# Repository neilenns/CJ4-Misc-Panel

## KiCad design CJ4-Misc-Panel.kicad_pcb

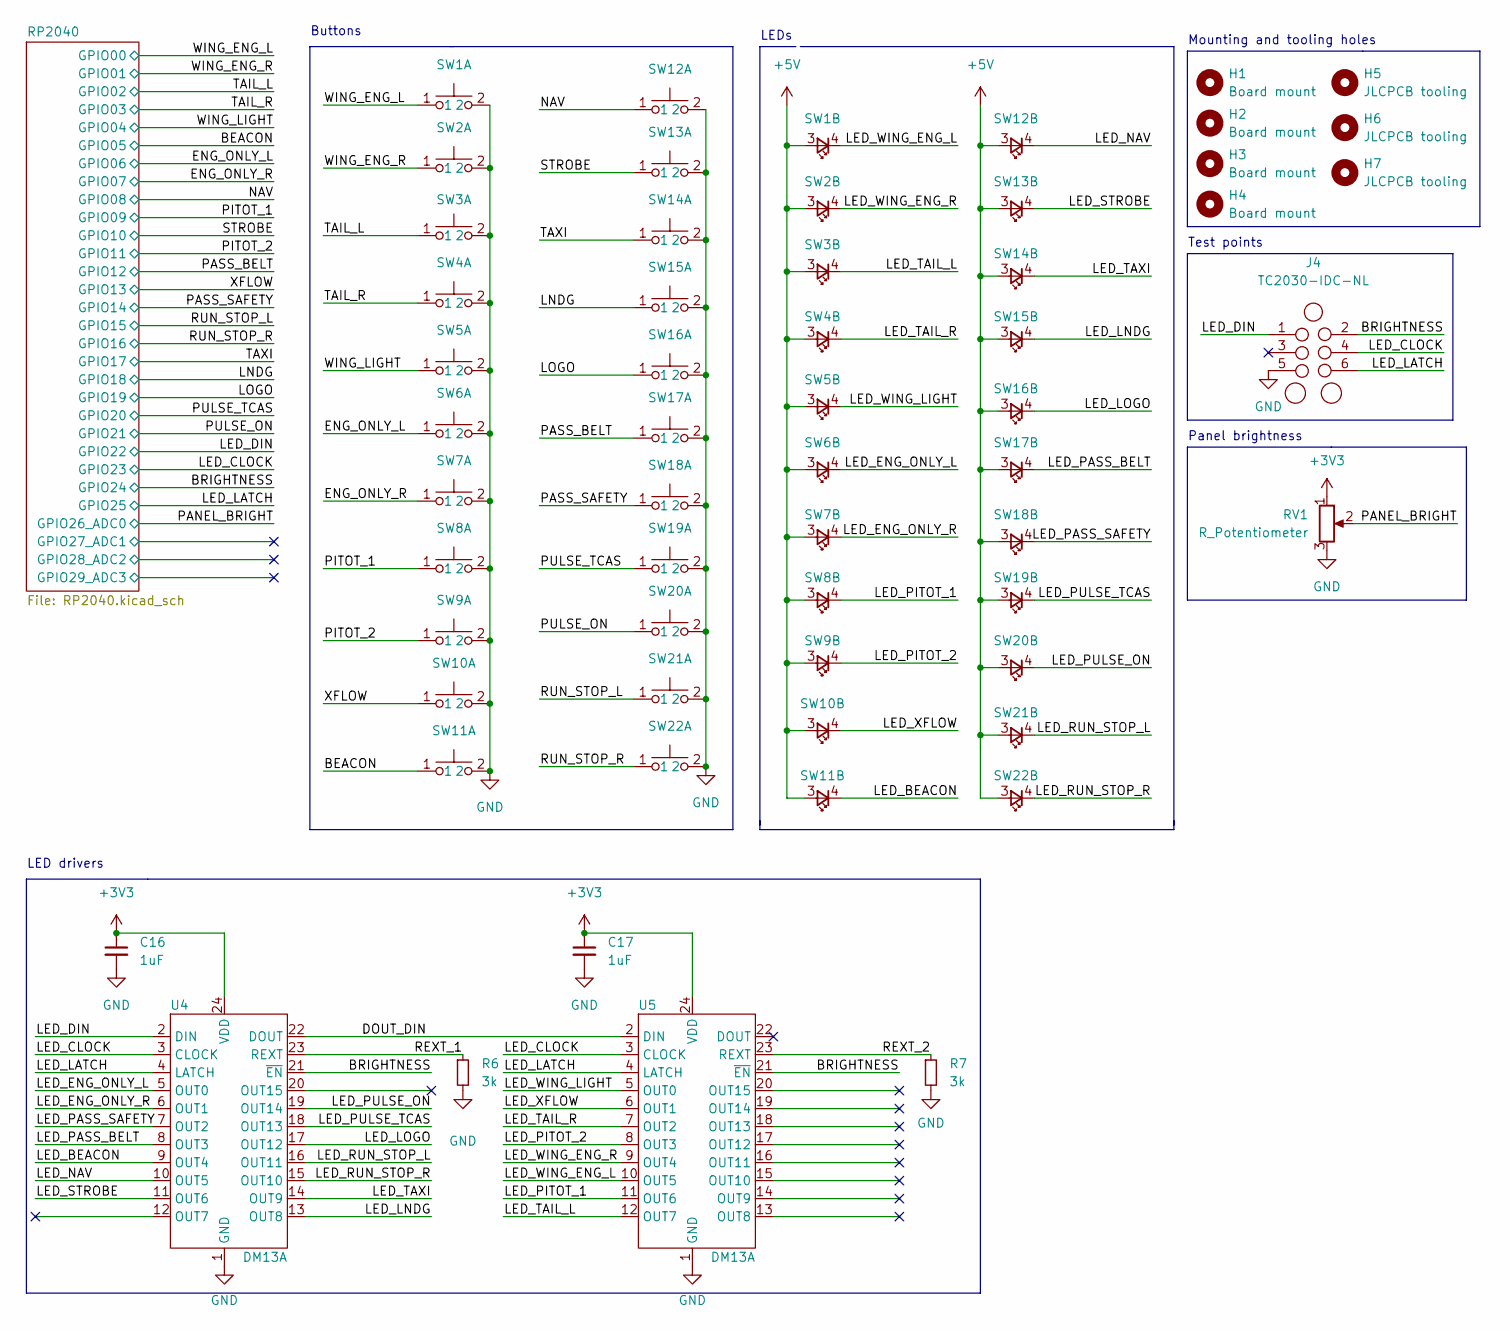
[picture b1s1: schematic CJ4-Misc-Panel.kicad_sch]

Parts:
C16, C17: 1uF; Perfect_0402; MPN - JLCPCB C52923
H1, H2, H3, H4: Board mount; MountingHole_3.2mm_M3
H5, H6, H7: JLCPCB tooling; JLCPCB_Tooling_Hole
J4: TC2030-IDC-NL; Tag-Connect_TC2030-IDC-NL_2x03_P1.27mm_Vertical
R6, R7: 3k; R_0805_2012Metric_Pad1.20x1.40mm_HandSolder; MPN - JLCPCB C17661; JLC 0805
RV1: R_Potentiometer; Potentiometer_Bourns_PTV09A-1_Single_Vertical
SW1, SW2, SW3, SW4, SW5, SW6, SW7, SW8, SW9, SW10, SW11, SW12, SW13, SW14, SW15, SW16, SW17, SW18, SW19, SW20, SW21, SW22: SW_PUSH_LED; SW_PUSH_LED_THT
U4, U5: DM13A; SSOP-24_3.9x8.7mm_P0.635mm

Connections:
+3V3: C16.1, C17.1, RV1.1, U4.24 (VDD), U5.24 (VDD); also elsewhere on the board
+5V: SW1.3, SW2.3, SW3.3, SW4.3, SW5.3, SW6.3, SW7.3, SW8.3, SW9.3, SW10.3, SW11.3, SW12.3, SW13.3, SW14.3, SW15.3, SW16.3, SW17.3, SW18.3, SW19.3, SW20.3, SW21.3, SW22.3; also elsewhere on the board
/BEACON: SW11.1; also elsewhere on the board
/BRIGHTNESS: J4.2, U4.21 (~EN), U5.21 (~EN); also elsewhere on the board
/DOUT_DIN: U4.22 (DOUT), U5.2 (DIN)
/ENG_ONLY_L: SW6.1; also elsewhere on the board
/ENG_ONLY_R: SW7.1; also elsewhere on the board
/LED_BEACON: SW11.4, U4.9 (OUT4)
/LED_CLOCK: J4.4, U4.3 (CLOCK), U5.3 (CLOCK); also elsewhere on the board
/LED_DIN: J4.1, U4.2 (DIN); also elsewhere on the board
/LED_ENG_ONLY_L: SW6.4, U4.5 (OUT0)
/LED_ENG_ONLY_R: SW7.4, U4.6 (OUT1)
/LED_LATCH: J4.6, U4.4 (LATCH), U5.4 (LATCH); also elsewhere on the board
/LED_LNDG: SW15.4, U4.13 (OUT8)
/LED_LOGO: SW16.4, U4.17 (OUT12)
/LED_NAV: SW12.4, U4.10 (OUT5)
/LED_PASS_BELT: SW17.4, U4.8 (OUT3)
/LED_PASS_SAFETY: SW18.4, U4.7 (OUT2)
/LED_PITOT_1: SW8.4, U5.11 (OUT6)
/LED_PITOT_2: SW9.4, U5.8 (OUT3)
/LED_PULSE_ON: SW20.4, U4.19 (OUT14)
/LED_PULSE_TCAS: SW19.4, U4.18 (OUT13)
/LED_RUN_STOP_L: SW21.4, U4.16 (OUT11)
/LED_RUN_STOP_R: SW22.4, U4.15 (OUT10)
/LED_STROBE: SW13.4, U4.11 (OUT6)
/LED_TAIL_L: SW3.4, U5.12 (OUT7)
/LED_TAIL_R: SW4.4, U5.7 (OUT2)
/LED_TAXI: SW14.4, U4.14 (OUT9)
/LED_WING_ENG_L: SW1.4, U5.10 (OUT5)
/LED_WING_ENG_R: SW2.4, U5.9 (OUT4)
/LED_WING_LIGHT: SW5.4, U5.5 (OUT0)
/LED_XFLOW: SW10.4, U5.6 (OUT1)
/LNDG: SW15.1; also elsewhere on the board
/LOGO: SW16.1; also elsewhere on the board
/NAV: SW12.1; also elsewhere on the board
/PANEL_BRIGHT: RV1.2; also elsewhere on the board
/PASS_BELT: SW17.1; also elsewhere on the board
/PASS_SAFETY: SW18.1; also elsewhere on the board
/PITOT_1: SW8.1; also elsewhere on the board
/PITOT_2: SW9.1; also elsewhere on the board
/PULSE_ON: SW20.1; also elsewhere on the board
/PULSE_TCAS: SW19.1; also elsewhere on the board
/REXT_1: R6.1, U4.23 (REXT)
/REXT_2: R7.1, U5.23 (REXT)
/RUN_STOP_L: SW21.1; also elsewhere on the board
/RUN_STOP_R: SW22.1; also elsewhere on the board
/STROBE: SW13.1; also elsewhere on the board
/TAIL_L: SW3.1; also elsewhere on the board
/TAIL_R: SW4.1; also elsewhere on the board
/TAXI: SW14.1; also elsewhere on the board
/WING_ENG_L: SW1.1; also elsewhere on the board
/WING_ENG_R: SW2.1; also elsewhere on the board
/WING_LIGHT: SW5.1; also elsewhere on the board
/XFLOW: SW10.1; also elsewhere on the board
GND: C16.2, C17.2, J4.5, R6.2, R7.2, RV1.3, SW1.2, SW2.2, SW3.2, SW4.2, SW5.2, SW6.2, SW7.2, SW8.2, SW9.2, SW10.2, SW11.2, SW12.2, SW13.2, SW14.2, SW15.2, SW16.2, SW17.2, SW18.2, SW19.2, SW20.2, SW21.2, SW22.2, U4.1 (GND), U5.1 (GND); also elsewhere on the board

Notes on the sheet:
LED drivers
Test points
Panel brightness
Buttons
LEDs
Mounting and tooling holes

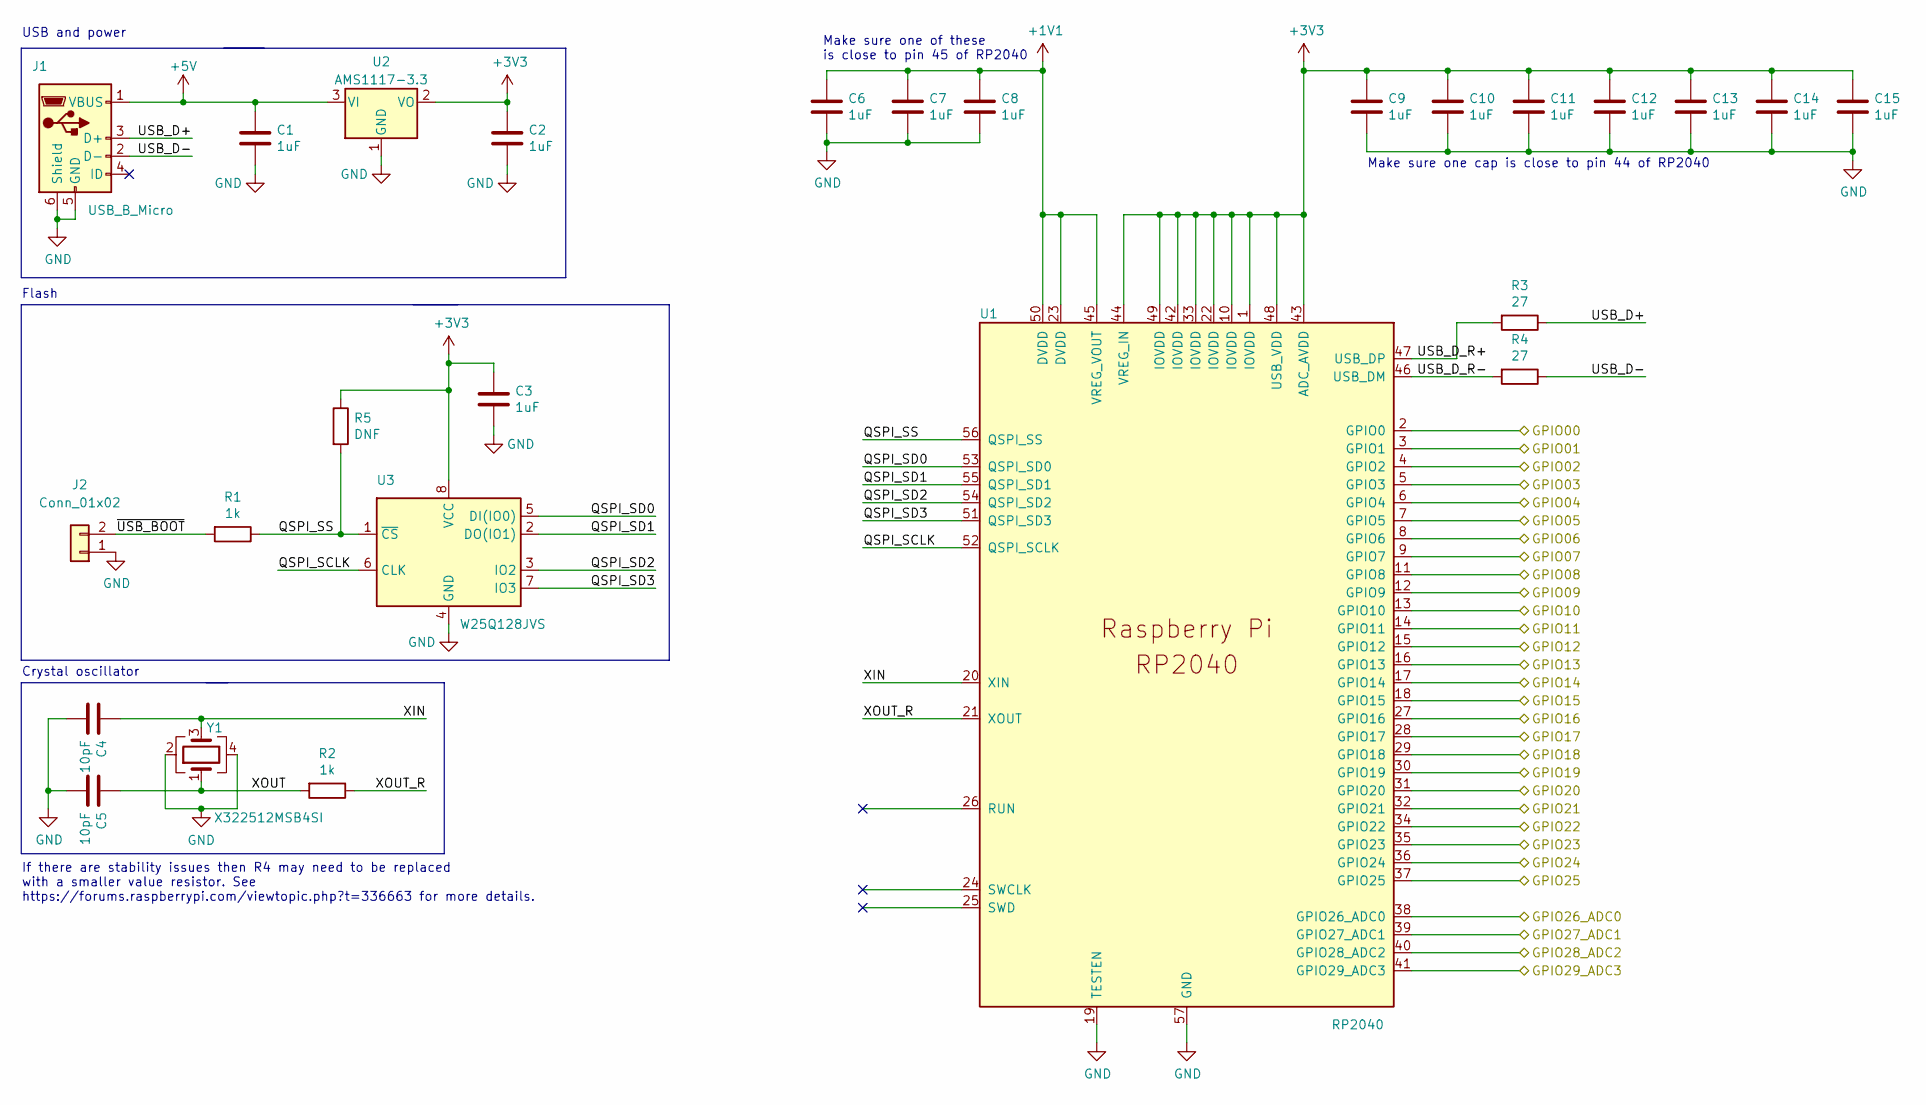
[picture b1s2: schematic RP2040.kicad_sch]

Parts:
C1, C2, C3, C6, C7, C8, C9, C10, C11, C12, C13, C14, C15: 1uF; Perfect_0402; MPN - JLCPCB C52923
C4, C5: 10pF; Perfect_0402; MPN - JLCPCB C32949
J1: USB_B_Micro; USB_B_Mini_Amphenol_UE25BE5510H
J2: Conn_01x02; PinHeader_1x02_P2.54mm_Vertical
R1, R2: 1k; Perfect_0402; MPN - JLCPCB C11702
R3, R4: 27; R_0603_1608Metric; MPN - JLCPCB C25190
R5: DNF; R_1206_3216Metric_Pad1.30x1.75mm_HandSolder
U1: RP2040; QFN56P40_700X700X90L40X18T310N; MPN - JLCPCB C2040
U2: AMS1117-3.3; SOT-223-3_TabPin2; MPN - JLCPCB C6186
U3: W25Q128JVS; SOIC-8_5.23x5.23mm_P1.27mm; MPN - JLCPCB C97521
Y1: X322512MSB4SI; Crystal_SMD_3225-4Pin_3.2x2.5mm; MPN - JLCPCB C9002

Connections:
+1V1: C6.1, C7.1, C8.1, U1.23 (DVDD), U1.45 (VREG_VOUT), U1.50 (DVDD)
+3V3: C2.1, C3.1, C9.1, C10.1, C11.1, C12.1, C13.1, C14.1, C15.1, R5.1, U1.1 (IOVDD), U1.10 (IOVDD), U1.22 (IOVDD), U1.33 (IOVDD), U1.42 (IOVDD), U1.43 (ADC_AVDD), U1.44 (VREG_IN), U1.48 (USB_VDD), U1.49 (IOVDD), U2.2 (VO), U3.8 (VCC); also elsewhere on the board
+5V: C1.1, J1.1 (VBUS), U2.3 (VI); also elsewhere on the board
/BEACON: U1.7 (GPIO5); also elsewhere on the board
/BRIGHTNESS: U1.36 (GPIO24); also elsewhere on the board
/ENG_ONLY_L: U1.8 (GPIO6); also elsewhere on the board
/ENG_ONLY_R: U1.9 (GPIO7); also elsewhere on the board
/LED_CLOCK: U1.35 (GPIO23); also elsewhere on the board
/LED_DIN: U1.34 (GPIO22); also elsewhere on the board
/LED_LATCH: U1.37 (GPIO25); also elsewhere on the board
/LNDG: U1.29 (GPIO18); also elsewhere on the board
/LOGO: U1.30 (GPIO19); also elsewhere on the board
/NAV: U1.11 (GPIO8); also elsewhere on the board
/PANEL_BRIGHT: U1.38 (GPIO26_ADC0); also elsewhere on the board
/PASS_BELT: U1.15 (GPIO12); also elsewhere on the board
/PASS_SAFETY: U1.17 (GPIO14); also elsewhere on the board
/PITOT_1: U1.12 (GPIO9); also elsewhere on the board
/PITOT_2: U1.14 (GPIO11); also elsewhere on the board
/PULSE_ON: U1.32 (GPIO21); also elsewhere on the board
/PULSE_TCAS: U1.31 (GPIO20); also elsewhere on the board
/RP2040/GPIO27_ADC1: U1.39 (GPIO27_ADC1)
/RP2040/GPIO28_ADC2: U1.40 (GPIO28_ADC2)
/RP2040/GPIO29_ADC3: U1.41 (GPIO29_ADC3)
/RP2040/QSPI_SCLK: U1.52 (QSPI_SCLK), U3.6 (CLK)
/RP2040/QSPI_SD0: U1.53 (QSPI_SD0), U3.5 (DI(IO0))
/RP2040/QSPI_SD1: U1.55 (QSPI_SD1), U3.2 (DO(IO1))
/RP2040/QSPI_SD2: U1.54 (QSPI_SD2), U3.3 (IO2)
/RP2040/QSPI_SD3: U1.51 (QSPI_SD3), U3.7 (IO3)
/RP2040/QSPI_SS: R1.1, R5.2, U1.56 (QSPI_SS), U3.1 (~CS)
/RP2040/USB_D+: J1.3 (D+), R3.1
/RP2040/USB_D-: J1.2 (D-), R4.1
/RP2040/USB_D_R+: R3.2, U1.47 (USB_DP)
/RP2040/USB_D_R-: R4.2, U1.46 (USB_DM)
/RP2040/XIN: C4.1, U1.20 (XIN), Y1.3
/RP2040/XOUT: C5.1, R2.2, Y1.1
/RP2040/XOUT_R: R2.1, U1.21 (XOUT)
/RP2040/~USB_BOOT: J2.2, R1.2
/RUN_STOP_L: U1.18 (GPIO15); also elsewhere on the board
/RUN_STOP_R: U1.27 (GPIO16); also elsewhere on the board
/STROBE: U1.13 (GPIO10); also elsewhere on the board
/TAIL_L: U1.4 (GPIO2); also elsewhere on the board
/TAIL_R: U1.5 (GPIO3); also elsewhere on the board
/TAXI: U1.28 (GPIO17); also elsewhere on the board
/WING_ENG_L: U1.2 (GPIO0); also elsewhere on the board
/WING_ENG_R: U1.3 (GPIO1); also elsewhere on the board
/WING_LIGHT: U1.6 (GPIO4); also elsewhere on the board
/XFLOW: U1.16 (GPIO13); also elsewhere on the board
GND: C1.2, C2.2, C3.2, C4.2, C5.2, C6.2, C7.2, C8.2, C9.2, C10.2, C11.2, C12.2, C13.2, C14.2, C15.2, J1.5 (GND), J1.6 (Shield), J2.1, U1.19 (TESTEN), U1.57 (GND), U2.1 (GND), U3.4 (GND), Y1.2, Y1.4; also elsewhere on the board

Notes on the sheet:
Make sure one of these is close to pin 45 of RP2040
USB and power
Make sure one cap is close to pin 44 of RP2040
If there are stability issues then R4 may need to be replaced with a smaller value resistor. See https://forums.raspberrypi.com/viewtopic.php?t=336663 for more details.
Flash
Crystal oscillator

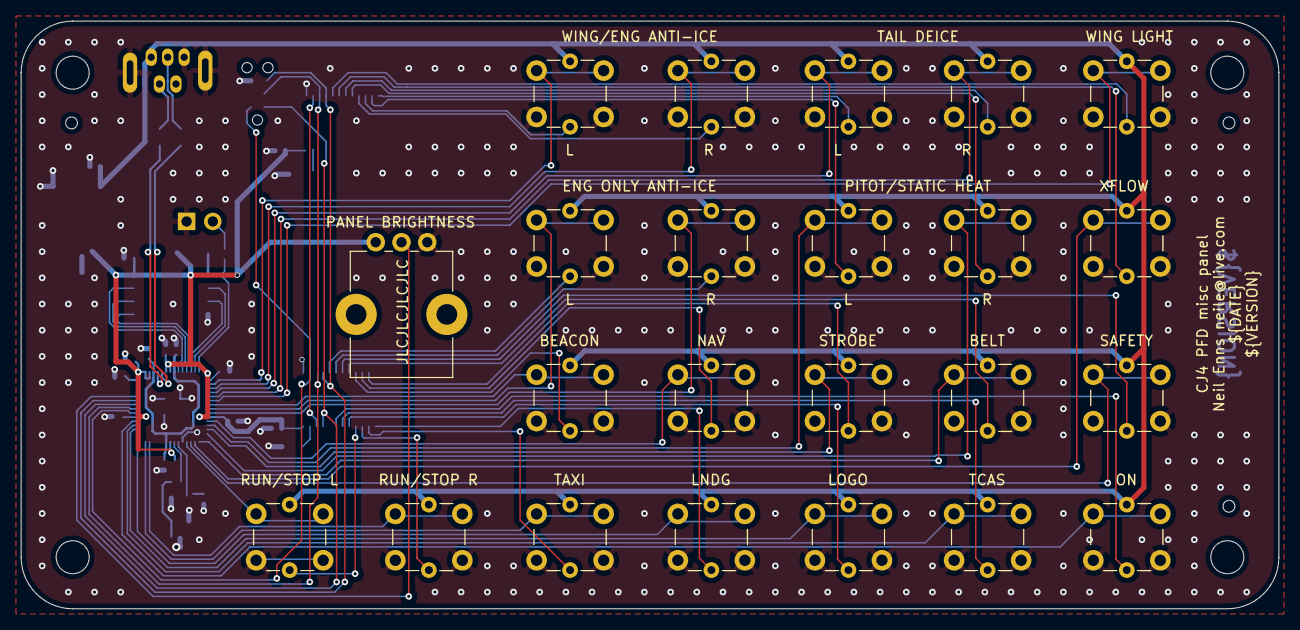
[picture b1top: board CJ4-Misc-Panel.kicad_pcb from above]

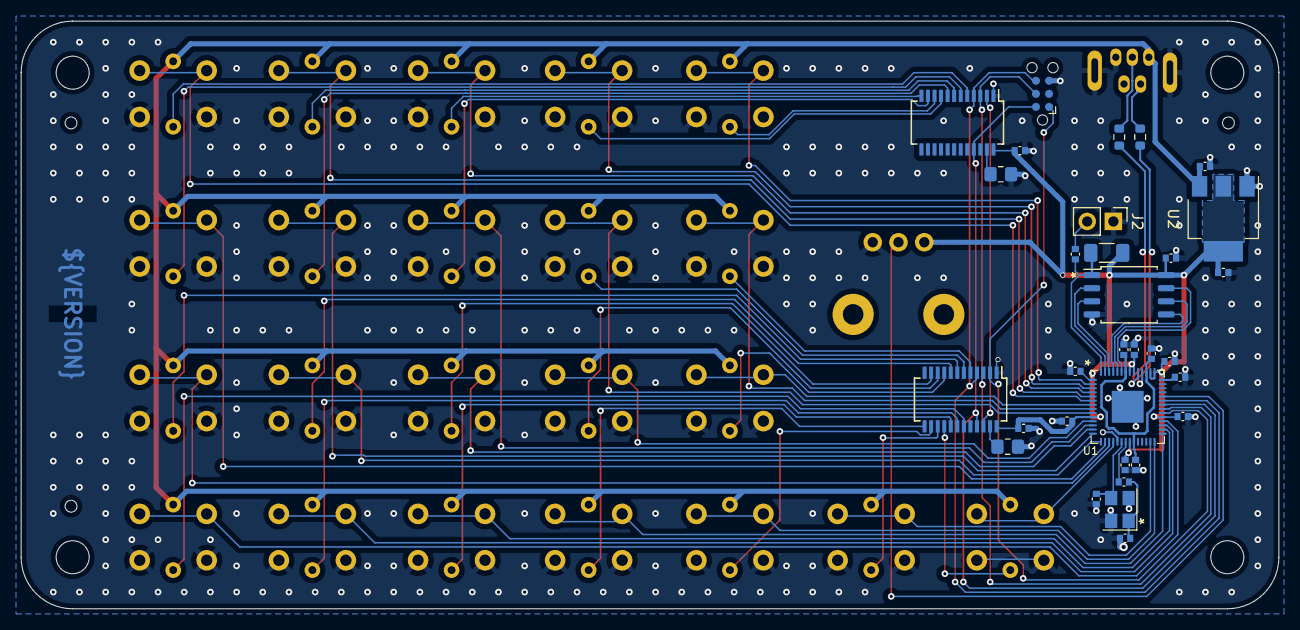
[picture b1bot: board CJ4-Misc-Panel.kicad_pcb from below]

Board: 2 copper layers, 122.0 x 57.0 mm, 63 parts (33 on the bottom side), 70 nets.

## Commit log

2023-01-02 First pass of work
2023-01-03 All the buttons are routed. Ugly, but routed.
2023-01-04 Fully routed!!!
2023-01-04 Cleanly routed
2023-01-05 Final routing, updated JLCPCB rotations
2023-01-05 Add JLC order number placement
2023-01-05 Fix JLCPCB BOM generation
2023-01-05 Fix rotations. GRRR.
2023-02-13 Updates and labels
2025-02-25 Add renovate.json
